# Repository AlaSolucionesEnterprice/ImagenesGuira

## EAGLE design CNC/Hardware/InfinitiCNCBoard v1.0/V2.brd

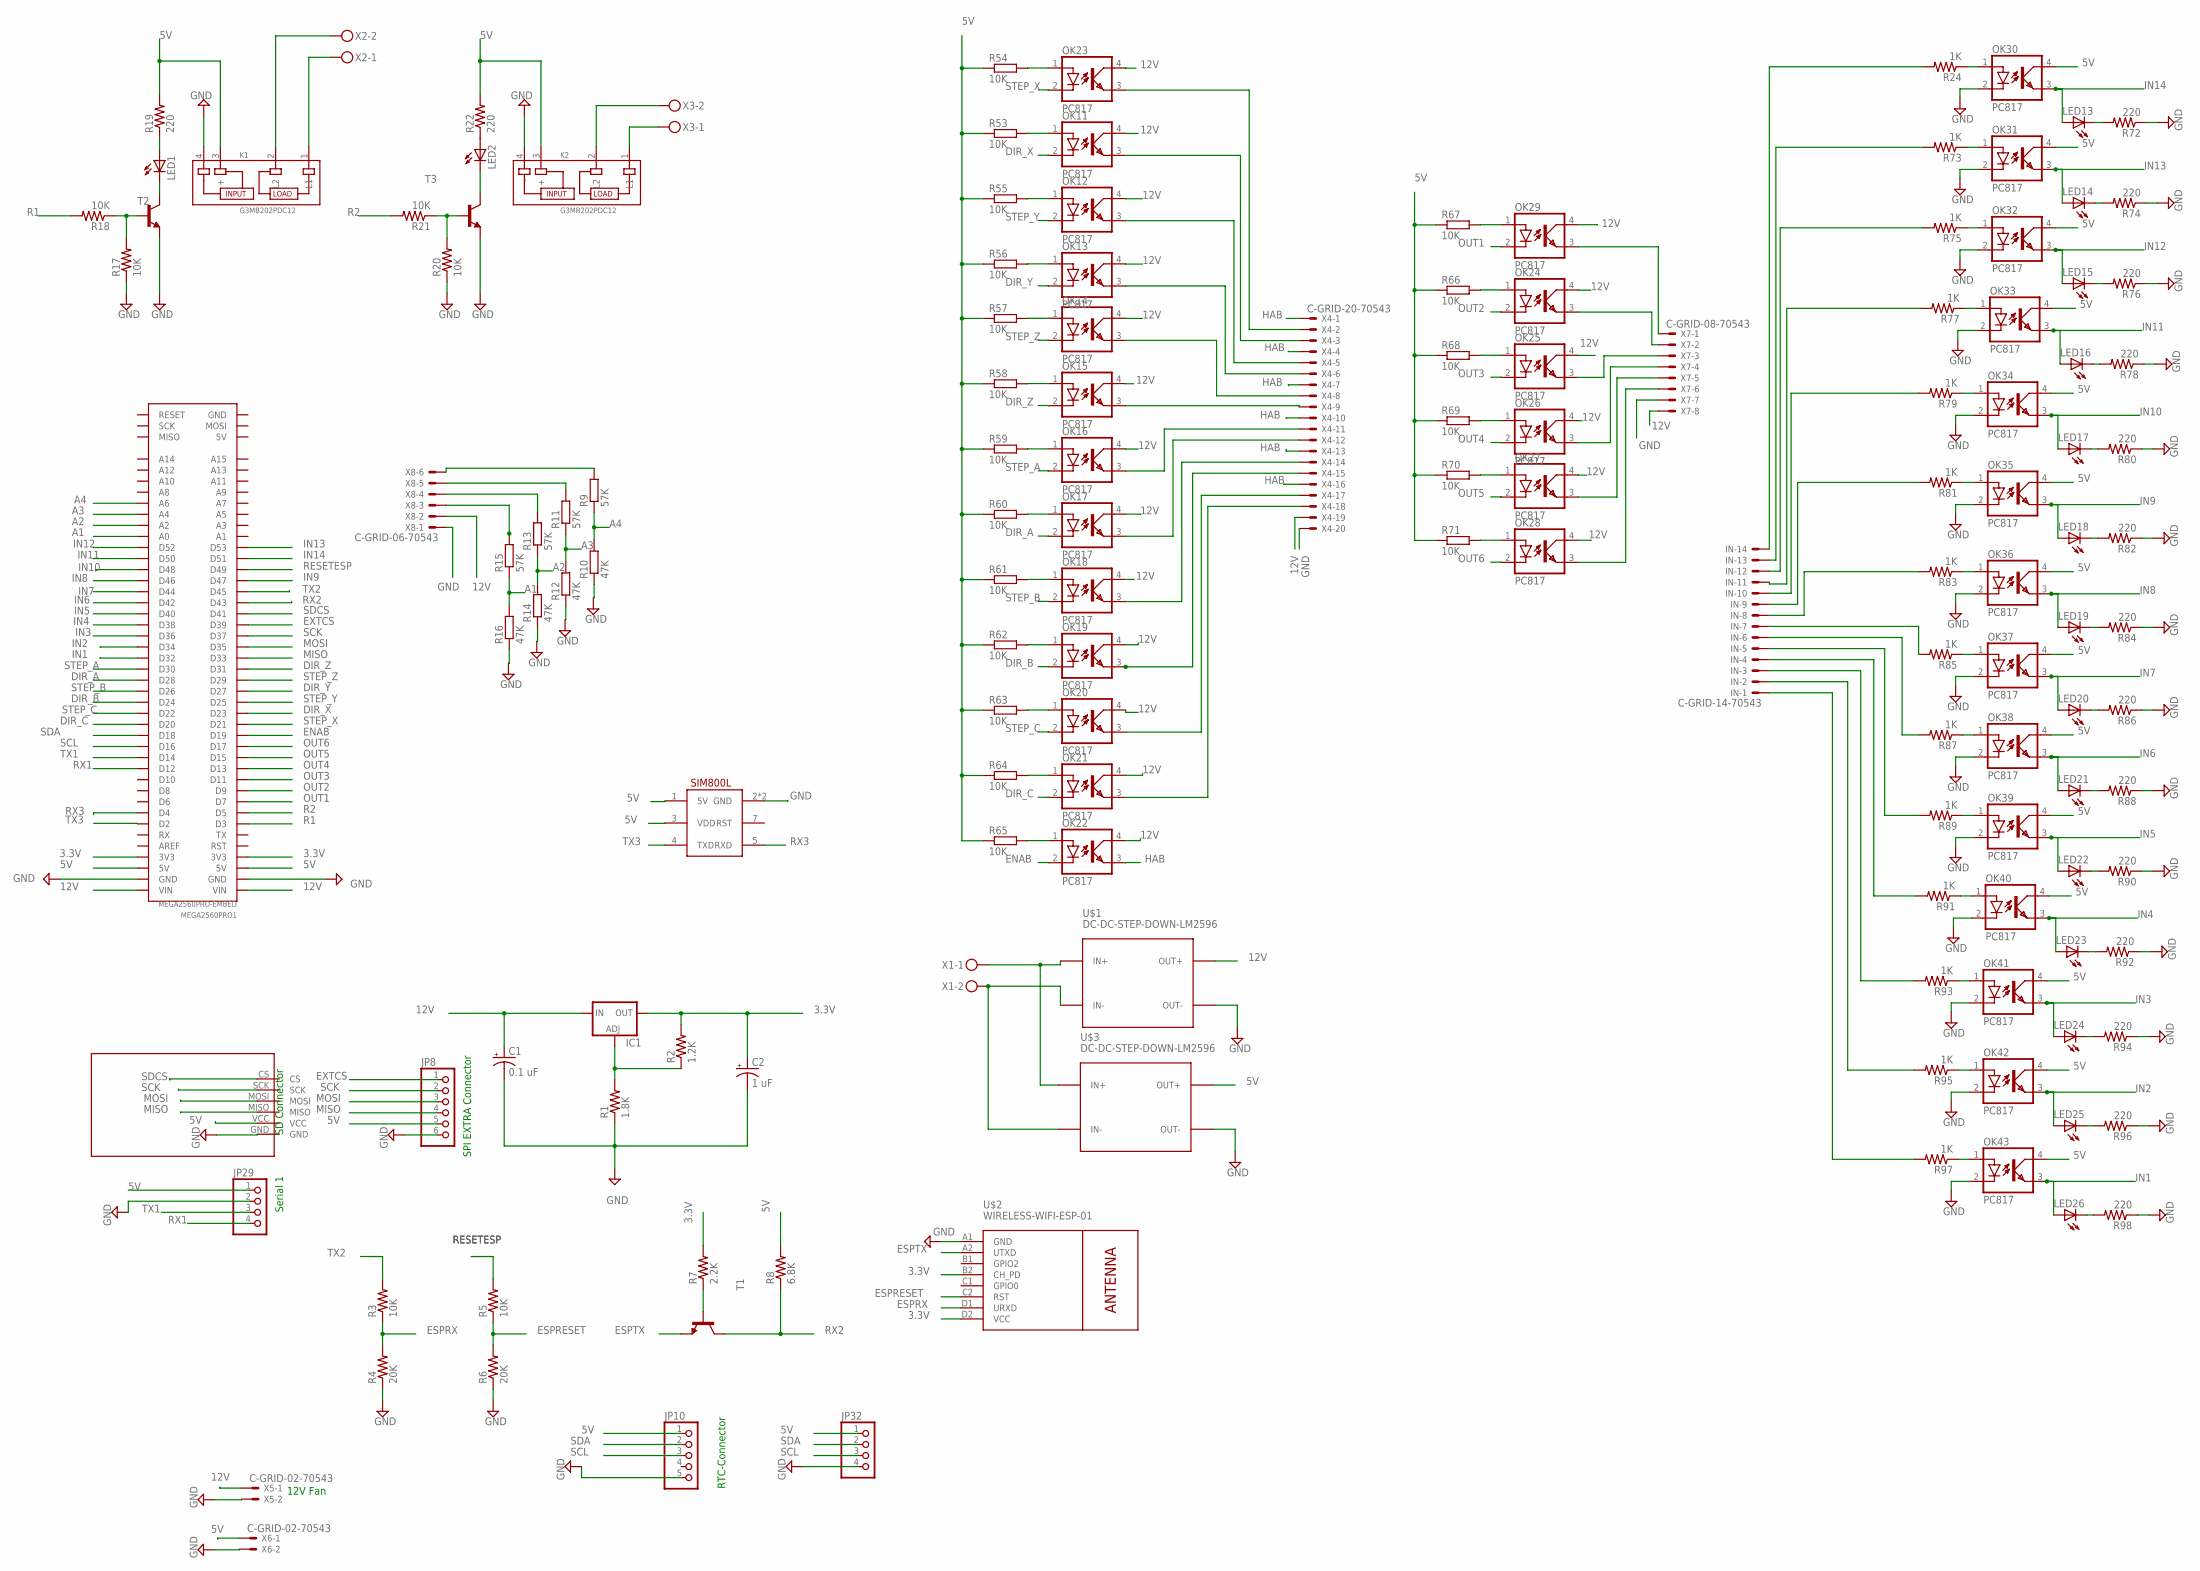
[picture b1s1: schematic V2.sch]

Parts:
C1: 0.1 uF; E2,5-7
C2: 1 uF; E2,5-7
IC1: LM317TL; 317TL
IN: C-GRID-14-70543; 70543-14
JP8: PINHD-1X6; 1X06
JP10: PINHD-1X5; 1X05
JP29, JP32: PINHD-1X4; 1X04
K1, K2: G3MB202PDC12; RELAY_G3MB202PDC12
LED1, LED2, LED13, LED14, LED15, LED16, LED17, LED18, LED19, LED20, LED21, LED22, LED23, LED24, LED25, LED26: LED3MM
MEGA2560PRO1: MEGA2560PRO-EMBED
OK11, OK12, OK13, OK14, OK15, OK16, OK17, OK18, OK19, OK20, OK21, OK22, OK23, OK24, OK25, OK26, OK27, OK28, OK29, OK30, OK31, OK32, OK33, OK34, OK35, OK36, OK37, OK38, OK39, OK40, OK41, OK42, OK43: PC817; DIL04
R1: 1.8K; 0207/10
R2: 1.2K; 0207/10
R3, R5, R17, R18, R20, R21: 10K; 0207/10
R4, R6: 20K; 0207/10
R7: 2.2K; 0207/10
R8: 6.8K; 0207/10
R9, R11, R13, R15: 57K; 0207/7
R10, R12, R14, R16: 47K; 0207/7
R19, R22, R72, R74, R76, R78, R80, R82, R84, R86, R88, R90, R92, R94, R96, R98: 220; 0207/10
R24, R73, R75, R77, R79, R81, R83, R85, R87, R89, R91, R93, R95, R97: 1K; 0207/10
R53, R54, R55, R56, R57, R58, R59, R60, R61, R62, R63, R64, R65, R66, R67, R68, R69, R70, R71: 10K; 0207/7
T1, T2, T3: 29-NPN-TO92-EBC; TO92-EBC
U$1, U$3: DC-DC-STEP-DOWN-LM2596
U$2: WIRELESS-WIFI-ESP-01
U$4: SIM800L; SIP
U$9: MODULO_SD
X1, X2, X3: MKDSN1,5/2-5,08
X4: C-GRID-20-70543; 70543-20
X5, X6: C-GRID-02-70543; 70543-02
X7: C-GRID-08-70543; 70543-08
X8: C-GRID-06-70543; 70543-06

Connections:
3.3V: C2.+, IC1.2 (OUT), MEGA2560PRO1.3V3@1 (3V3), MEGA2560PRO1.3V3@2 (3V3), R2.2, R7.2, U$2.B2 (CH_PD), U$2.D2 (VCC)
5V: JP8.5, JP10.1, JP29.1, JP32.1, K1.3 (+), K2.3 (+), MEGA2560PRO1.5V@1 (5V), MEGA2560PRO1.5V@2 (5V), OK30.4 (COL), OK31.4 (COL), OK32.4 (COL), OK33.4 (COL), OK34.4 (COL), OK35.4 (COL), OK36.4 (COL), OK37.4 (COL), OK38.4 (COL), OK39.4 (COL), OK40.4 (COL), OK41.4 (COL), OK42.4 (COL), OK43.4 (COL), R8.2, R19.2, R22.2, R53.1, R54.1, R55.1, R56.1, R57.1, R58.1, R59.1, R60.1, R61.1, R62.1, R63.1, R64.1, R65.1, R66.1, R67.1, R68.1, R69.1, R70.1, R71.1, U$3.OUT+, U$4.1 (5V), U$4.3 (VDD), U$9.VCC, X6.1
12V: C1.+, IC1.3 (IN), MEGA2560PRO1.VIN@1 (VIN), MEGA2560PRO1.VIN@2 (VIN), OK11.4 (COL), OK12.4 (COL), OK13.4 (COL), OK14.4 (COL), OK15.4 (COL), OK16.4 (COL), OK17.4 (COL), OK18.4 (COL), OK19.4 (COL), OK20.4 (COL), OK21.4 (COL), OK22.4 (COL), OK23.4 (COL), OK24.4 (COL), OK25.4 (COL), OK26.4 (COL), OK27.4 (COL), OK28.4 (COL), OK29.4 (COL), U$1.OUT+, X4.19, X5.1, X7.8, X8.2
A1: MEGA2560PRO1.A0, R15.1, R16.2
A2: MEGA2560PRO1.A2, R13.1, R14.2
A3: MEGA2560PRO1.A4, R11.1, R12.2
A4: MEGA2560PRO1.A6, R9.1, R10.2
DIR_A: MEGA2560PRO1.D28, OK17.2 (C)
DIR_B: MEGA2560PRO1.D24, OK19.2 (C)
DIR_C: MEGA2560PRO1.D20, OK21.2 (C)
DIR_X: MEGA2560PRO1.D23, OK11.2 (C)
DIR_Y: MEGA2560PRO1.D27, OK13.2 (C)
DIR_Z: MEGA2560PRO1.D31, OK15.2 (C)
ENAB: MEGA2560PRO1.D19, OK22.2 (C)
ESPRESET: R5.1, R6.2, U$2.C2 (RST)
ESPRX: R3.1, R4.2, U$2.D1 (URXD)
ESPTX: T1.E, U$2.A2 (UTXD)
EXTCS: JP8.1, MEGA2560PRO1.D39
GND: C1.-, C2.-, JP8.6, JP10.5, JP29.2, JP32.4, K1.4 (-), K2.4 (-), MEGA2560PRO1.GND@1 (GND), MEGA2560PRO1.GND@2 (GND), OK30.2 (C), OK31.2 (C), OK32.2 (C), OK33.2 (C), OK34.2 (C), OK35.2 (C), OK36.2 (C), OK37.2 (C), OK38.2 (C), OK39.2 (C), OK40.2 (C), OK41.2 (C), OK42.2 (C), OK43.2 (C), R1.1, R4.1, R6.1, R10.1, R12.1, R14.1, R16.1, R17.1, R20.1, R72.1, R74.1, R76.1, R78.1, R80.1, R82.1, R84.1, R86.1, R88.1, R90.1, R92.1, R94.1, R96.1, R98.1, T2.E, T3.E, U$1.OUT-, U$2.A1 (GND), U$3.OUT-, U$4.2 (GND), U$4.6 (GND), U$9.GND, X4.20, X5.2, X6.2, X7.7, X8.1
HAB: OK22.3 (EMIT), X4.1, X4.4, X4.7, X4.10, X4.13, X4.16
IN1: LED26.A, MEGA2560PRO1.D32, OK43.3 (EMIT)
IN2: LED25.A, MEGA2560PRO1.D34, OK42.3 (EMIT)
IN3: LED24.A, MEGA2560PRO1.D36, OK41.3 (EMIT)
IN4: LED23.A, MEGA2560PRO1.D38, OK40.3 (EMIT)
IN5: LED22.A, MEGA2560PRO1.D40, OK39.3 (EMIT)
IN6: LED21.A, MEGA2560PRO1.D42, OK38.3 (EMIT)
IN7: LED20.A, MEGA2560PRO1.D44, OK37.3 (EMIT)
IN8: LED19.A, MEGA2560PRO1.D46, OK36.3 (EMIT)
IN9: LED18.A, MEGA2560PRO1.D47, OK35.3 (EMIT)
IN10: LED17.A, MEGA2560PRO1.D48, OK34.3 (EMIT)
IN11: LED16.A, MEGA2560PRO1.D50, OK33.3 (EMIT)
IN12: LED15.A, MEGA2560PRO1.D52, OK32.3 (EMIT)
IN13: LED14.A, MEGA2560PRO1.D53, OK31.3 (EMIT)
IN14: LED13.A, MEGA2560PRO1.D51, OK30.3 (EMIT)
MISO: JP8.4, MEGA2560PRO1.D33, U$9.MISO
MOSI: JP8.3, MEGA2560PRO1.D35, U$9.MOSI
unnamed: K1.1 (L1), X2.1
unnamed: R7.1, T1.B
unnamed: IC1.1 (ADJ), R1.2, R2.1
unnamed: U$1.IN+, U$3.IN+, X1.1
unnamed: U$1.IN-, U$3.IN-, X1.2
unnamed: R17.2, R18.1, T2.B
unnamed: LED1.K (C), T2.C
unnamed: LED1.A, R19.1
unnamed: K1.2 (L2), X2.2
unnamed: K2.1 (L1), X3.1
unnamed: R20.2, R21.1, T3.B
unnamed: LED2.K (C), T3.C
unnamed: LED2.A, R22.1
unnamed: K2.2 (L2), X3.2
unnamed: OK23.1 (A), R54.2
unnamed: OK11.1 (A), R53.2
unnamed: R9.2, X8.6
unnamed: OK30.1 (A), R24.1
unnamed: R11.2, X8.5
unnamed: R13.2, X8.4
unnamed: R15.2, X8.3
unnamed: OK12.1 (A), R55.2
unnamed: OK29.3 (EMIT), X7.1
unnamed: OK24.3 (EMIT), X7.2
unnamed: OK25.3 (EMIT), X7.3
unnamed: OK13.1 (A), R56.2
unnamed: OK26.3 (EMIT), X7.4
unnamed: OK27.3 (EMIT), X7.5
unnamed: OK28.3 (EMIT), X7.6
unnamed: OK14.1 (A), R57.2
unnamed: OK23.3 (EMIT), X4.2
unnamed: OK11.3 (EMIT), X4.3
unnamed: OK12.3 (EMIT), X4.5
unnamed: OK15.1 (A), R58.2
unnamed: OK13.3 (EMIT), X4.6
unnamed: OK14.3 (EMIT), X4.8
unnamed: OK15.3 (EMIT), X4.9
unnamed: OK16.1 (A), R59.2
unnamed: OK16.3 (EMIT), X4.11
unnamed: OK17.3 (EMIT), X4.12
unnamed: OK18.3 (EMIT), X4.14
unnamed: OK20.3 (EMIT), X4.17
unnamed: OK17.1 (A), R60.2
unnamed: OK21.3 (EMIT), X4.18
unnamed: OK18.1 (A), R61.2
unnamed: OK19.1 (A), R62.2
unnamed: OK20.1 (A), R63.2
unnamed: OK21.1 (A), R64.2
unnamed: OK22.1 (A), R65.2
unnamed: OK19.3 (EMIT), X4.15
unnamed: OK29.1 (A), R67.2
unnamed: OK24.1 (A), R66.2
unnamed: OK25.1 (A), R68.2
unnamed: OK26.1 (A), R69.2
unnamed: OK27.1 (A), R70.2
unnamed: OK28.1 (A), R71.2
unnamed: LED13.K (C), R72.2
unnamed: OK31.1 (A), R73.1
unnamed: LED14.K (C), R74.2
unnamed: OK32.1 (A), R75.1
unnamed: LED15.K (C), R76.2
unnamed: OK33.1 (A), R77.1
unnamed: LED16.K (C), R78.2
unnamed: OK34.1 (A), R79.1
unnamed: LED17.K (C), R80.2
unnamed: OK35.1 (A), R81.1
unnamed: LED18.K (C), R82.2
unnamed: OK36.1 (A), R83.1
unnamed: LED19.K (C), R84.2
unnamed: OK37.1 (A), R85.1
unnamed: LED20.K (C), R86.2
unnamed: OK38.1 (A), R87.1
unnamed: LED21.K (C), R88.2
unnamed: OK39.1 (A), R89.1
unnamed: LED22.K (C), R90.2
unnamed: OK40.1 (A), R91.1
unnamed: LED23.K (C), R92.2
unnamed: OK41.1 (A), R93.1
unnamed: LED24.K (C), R94.2
unnamed: OK42.1 (A), R95.1
unnamed: LED25.K (C), R96.2
unnamed: OK43.1 (A), R97.1
unnamed: LED26.K (C), R98.2
unnamed: IN.14, R24.2
unnamed: IN.13, R73.2
unnamed: IN.12, R75.2
unnamed: IN.11, R77.2
unnamed: IN.10, R79.2
unnamed: IN.9, R81.2
unnamed: IN.8, R83.2
unnamed: IN.7, R85.2
unnamed: IN.6, R87.2
unnamed: IN.5, R89.2
unnamed: IN.4, R91.2
unnamed: IN.3, R93.2
unnamed: IN.2, R95.2
unnamed: IN.1, R97.2
OUT1: MEGA2560PRO1.D7, OK29.2 (C)
OUT2: MEGA2560PRO1.D9, OK24.2 (C)
OUT3: MEGA2560PRO1.D11, OK25.2 (C)
OUT4: MEGA2560PRO1.D13, OK26.2 (C)
OUT5: MEGA2560PRO1.D15, OK27.2 (C)
OUT6: MEGA2560PRO1.D17, OK28.2 (C)
R1: MEGA2560PRO1.D3, R18.2
R2: MEGA2560PRO1.D5, R21.2
RESETESP: MEGA2560PRO1.D49, R5.2
RX1: JP29.4, MEGA2560PRO1.D12
RX2: MEGA2560PRO1.D43, R8.1, T1.C
RX3: MEGA2560PRO1.D4, U$4.5 (RXD)
SCK: JP8.2, MEGA2560PRO1.D37, U$9.SCK
SCL: JP10.3, JP32.3, MEGA2560PRO1.D16
SDA: JP10.2, JP32.2, MEGA2560PRO1.D18
SDCS: MEGA2560PRO1.D41, U$9.CS
STEP_A: MEGA2560PRO1.D30, OK16.2 (C)
STEP_B: MEGA2560PRO1.D26, OK18.2 (C)
STEP_C: MEGA2560PRO1.D22, OK20.2 (C)
STEP_X: MEGA2560PRO1.D21, OK23.2 (C)
STEP_Y: MEGA2560PRO1.D25, OK12.2 (C)
STEP_Z: MEGA2560PRO1.D29, OK14.2 (C)
TX1: JP29.3, MEGA2560PRO1.D14
TX2: MEGA2560PRO1.D45, R3.2
TX3: MEGA2560PRO1.D2, U$4.4 (TXD)

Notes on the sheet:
SD Connector
Serial 1
12V Fan
RTC-Connector
SPI EXTRA Connector

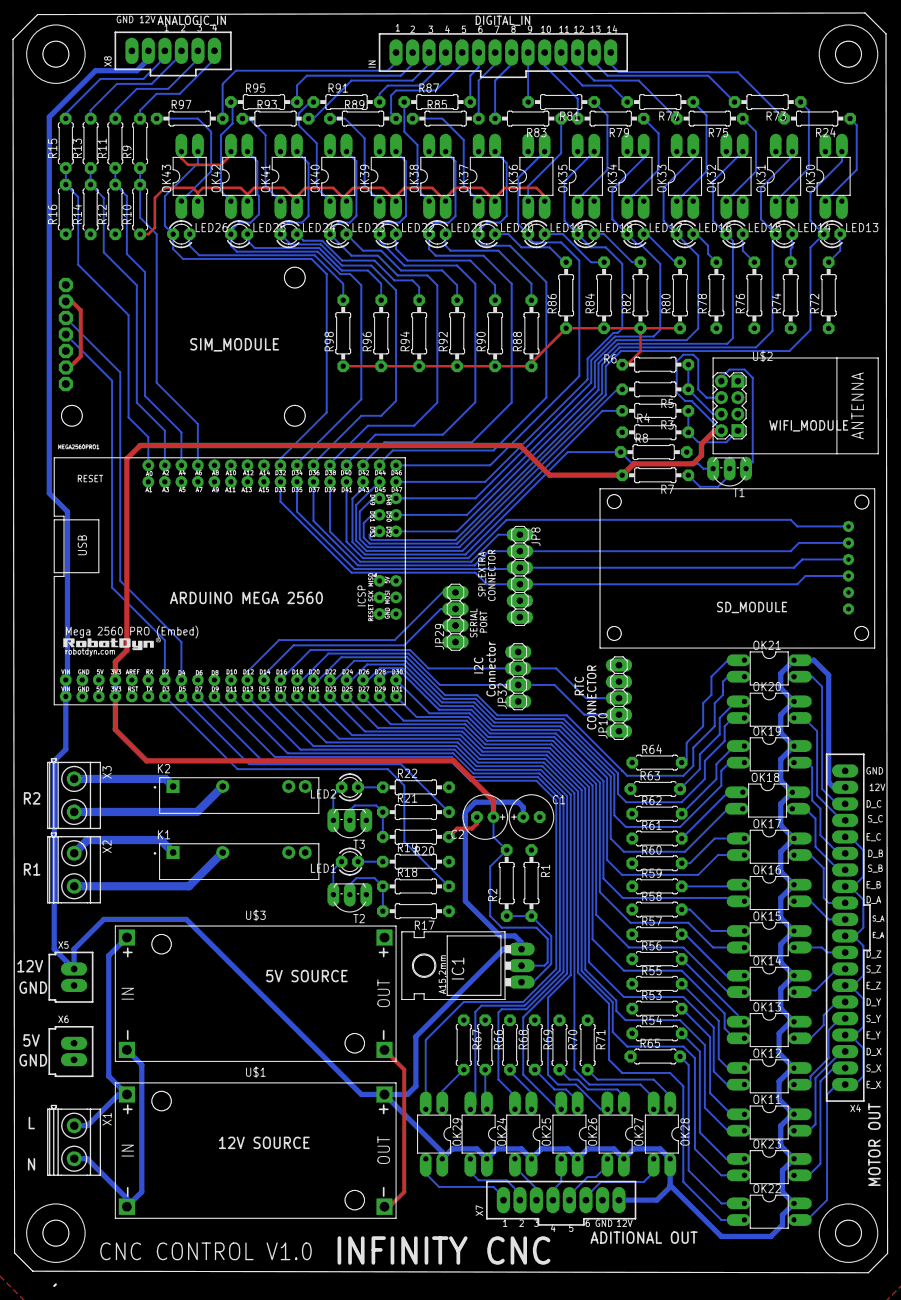
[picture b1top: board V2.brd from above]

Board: 2 copper layers, 134.2 x 195.7 mm, 149 parts (0 on the bottom side), 158 nets.

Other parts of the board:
U$5, U$6, U$7, U$8: DRIL-4

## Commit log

2021-07-21 firstAdd
2021-07-21 morePictAdded
2021-07-21 removeWrongDocumentation
2021-07-21 Added Documentation
2021-07-21 Added New Picts
2021-07-21 Added Old Picts
2021-07-21 Proj Tree Reestructured
2021-07-22 Added first version of CNC PCB design
2021-07-22 organizado directorio
2021-07-22 Borrar contenido
2021-07-26 Create Informe Levantamiento Previo 26-07-2021.docx
    Actualizacion del Informe d Levantaiento previo

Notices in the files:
parts and their libraries:
diy-modules DC-DC modules: Released under the Creative Commons Attribution 4.0 International License: http://creativecommons.org/licenses/by/4.0
